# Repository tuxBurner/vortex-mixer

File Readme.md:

# Vortex Paint Mixer

This is my OpenSource vortex paint mixer.

You can also find it on thingiverse: https://www.thingiverse.com/thing:3605287

The reason why i created this, is i wanted to have an easy way to shake my paints. I used an adapter on a jig saw, which worked pretty well but was verry noisy to.

I stumpled over the vortex mixer from NDubiel on thingiverse: https://www.thingiverse.com/thing:534894 which was quite good but i wanted to improve some stuff.

Look the video how it works

## Contribute

When you found a bug or have enhancement feel free to create a pull request or an issue :)

## Software used to create this project

* For 3d modelling: [http://openscad.org](http://openscad.org)
* For the pcb: [http://http://kicad.org/](http://kicad.org/)

I thank all the people which make it possible to create a project like this with there free software.

## Scad files

The case / lid and motorclamp scad file is the [scadfiles/case.scad](scadfiles/case.scad)

The top scad file is the [scadfiles/top.scad](scadfiles/top.scad)

## Howto build the mixer

### Tools

  * A 3d printer or use one of the services which print the objects for you
  * Soldering iron
  * Superglue
  * Hotglue gun
  * Optional if you want to create the pcb a mill or edging equipment

### Motorcontroller PCB Components

  * 1 x Diode (for example a 4007)
  * 1 x Poti 10K
  * 2 x Capacitor 47uF at 20V or greater 
  * 1 x LM317
  * 1 x Heatsink for the LM317 **required** 
  * 1 x 1k Resistor
  * 2 x Screw Terminal (Optional) 

### Other electronic Components

  * 12V DC Motor
  * Micro Switch
  * 1 x Powerplug (Optional) 
  * Poti Knob
  * 12 to 20 volt power supply

### General Components

  * 4 x Rubber Foot 
  * 1 x M3 * 30 Bolt + 3M Nut for the motor clamp
  * 5 x M3 tapping screws
  * Bearing for the cuppler
  * For the top 4M x 20 Bolt and 2 4M x Nuts

### Components to print

#### For the Mixer Case:

Print the following parts. Each one time.

I used 20% infill and PLA.

* [stls/case_bottom.stl](stls/case_bottom.stl)
* [stls/motor_clamp.stl](stls/motor_clamp.stl)
* [stls/wedge.stl](stls/wedge.stl)
* [stls/lid.stl](stls/lid.stl)
* [stls/coupler.stl](stls/coupler.stl)

#### For the paint bottle tops

Select the one which yo need.

I used 20% infill and PLA.

* [Vallejo](stls/tops/vallejo_top.stl)
* [Vallejo big bottle](stls/tops/vallejo_big_top.stl)
* [Games Workshop](stls/tops/games_workshop_top.stl)
* [Games Workshop old](stls/tops/games_workshop_old_top.stl)

## Motorcontroller PCB

The schemantics is like this

You can either use the pcb which i generated with KICAD. The project files are located in the folder: **[pcb](pcb)**

If you don't have the possibility to create the pcb you can also freewire the electronics.

## Build Instructions

### Mixer

Hot glue the micro switch into the case and wire the switch to the power plug.

Put the motorclamp and the motor together

Assemble the pcb. Don't forget the heatsink :)

Wire the wires to the pcb from the powerplug, micro switch and the motor.

Fix the poti with the nut onto the case.

Add the knob to the poti.

Add the wedge to the motor clamp. Mine broke a little bit when i tokked of the printer. But it is still working. 

¯\\_(ツ)_/¯

Screw the motorclamp into the case.

Screw the lid onto the case.

Superglue the bearing into the coupler.

Put the coupler onto the motor.

## Paint bottle top

Here is a picture of the diffrent tops and the corresponding paint bottles.

Put a M4 nut into the bottom of the top.

Screw a M4 bolt from the other side into the top and put a second M4 nut at the bottom. 

**DONE ! :)**

Just plugin the power and push down the color top into the coupler.

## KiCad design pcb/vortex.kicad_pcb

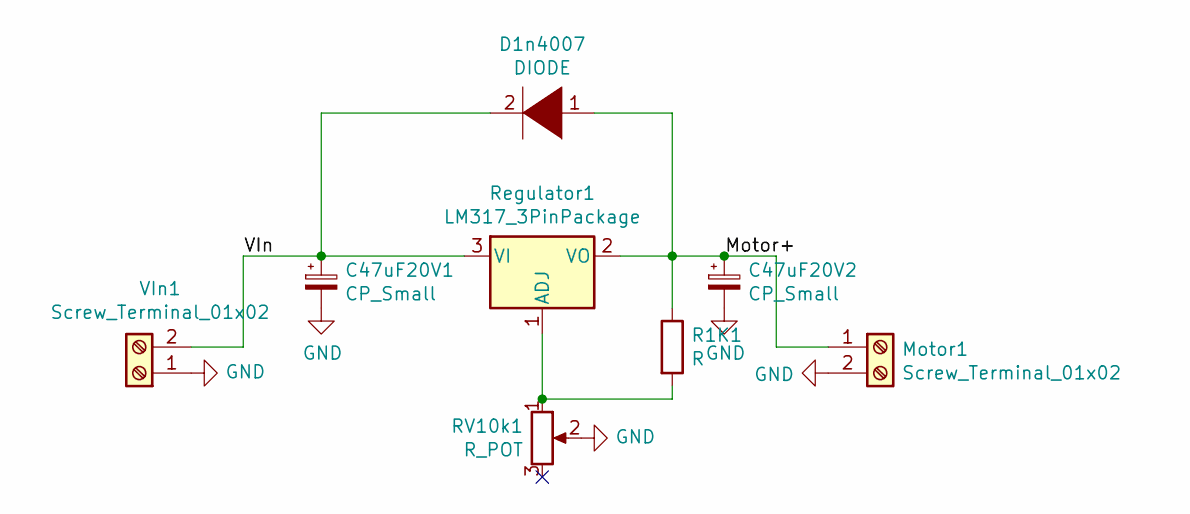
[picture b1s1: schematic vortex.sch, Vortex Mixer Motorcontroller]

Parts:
C47uF20V1, C47uF20V2: CP_Small; CP_Radial_D5.0mm_P2.50mm
D1n4007: DIODE; D_A-405_P7.62mm_Horizontal
Motor1: Screw_Terminal_01x02; TerminalBlock_bornier-2_P5.08mm
R1K1: R; R_Axial_DIN0207_L6.3mm_D2.5mm_P7.62mm_Horizontal
RV10k1: R_POT; Potentiometer_Alps_RK163_Single_Horizontal
Regulator1: LM317_3PinPackage; TO-220-3_Vertical
VIn1: Screw_Terminal_01x02; TerminalBlock_bornier-2_P5.08mm

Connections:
/Motor+: C47uF20V2.1, D1n4007.1 (K), Motor1.1, R1K1.1, Regulator1.2 (VO)
/VIn: C47uF20V1.1, D1n4007.2 (A), Regulator1.3 (VI), VIn1.2
GND: C47uF20V1.2, C47uF20V2.2, Motor1.2, RV10k1.2, VIn1.1
unnamed: R1K1.2, RV10k1.1, Regulator1.1 (ADJ)

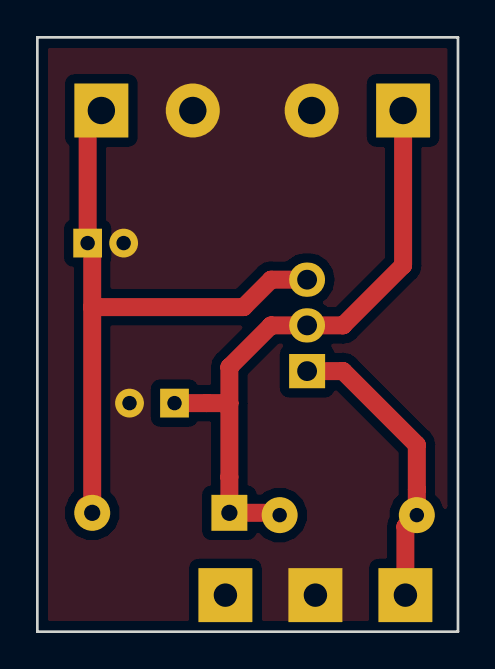
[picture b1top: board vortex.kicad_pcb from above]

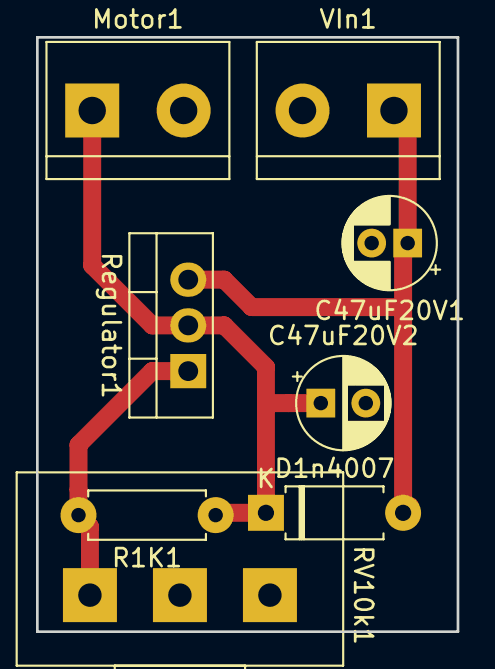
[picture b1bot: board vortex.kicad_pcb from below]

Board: 2 copper layers, 23.4 x 33.0 mm, 8 parts (8 on the bottom side), 4 nets.

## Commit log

2019-05-03 Added schemantic pcb to the Readme
2019-05-03 Added build images
2019-05-03 Resized the images
2019-05-03 Finished the readme
2019-05-03 Added thingiverse link
2021-11-08 Update Readme.md
    https://forum.kicad.info/t/warning-avoid-all-links-to-kicad-pcb-org-use-kicad-org/31521
